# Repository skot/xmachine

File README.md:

# The SE/30 Xmachine
* 1989 Apple Macintosh SE/30
* MC68030 PDS Card
* Lattice ECP5 FPGA

## Files
* Eagle Schematic and PCB

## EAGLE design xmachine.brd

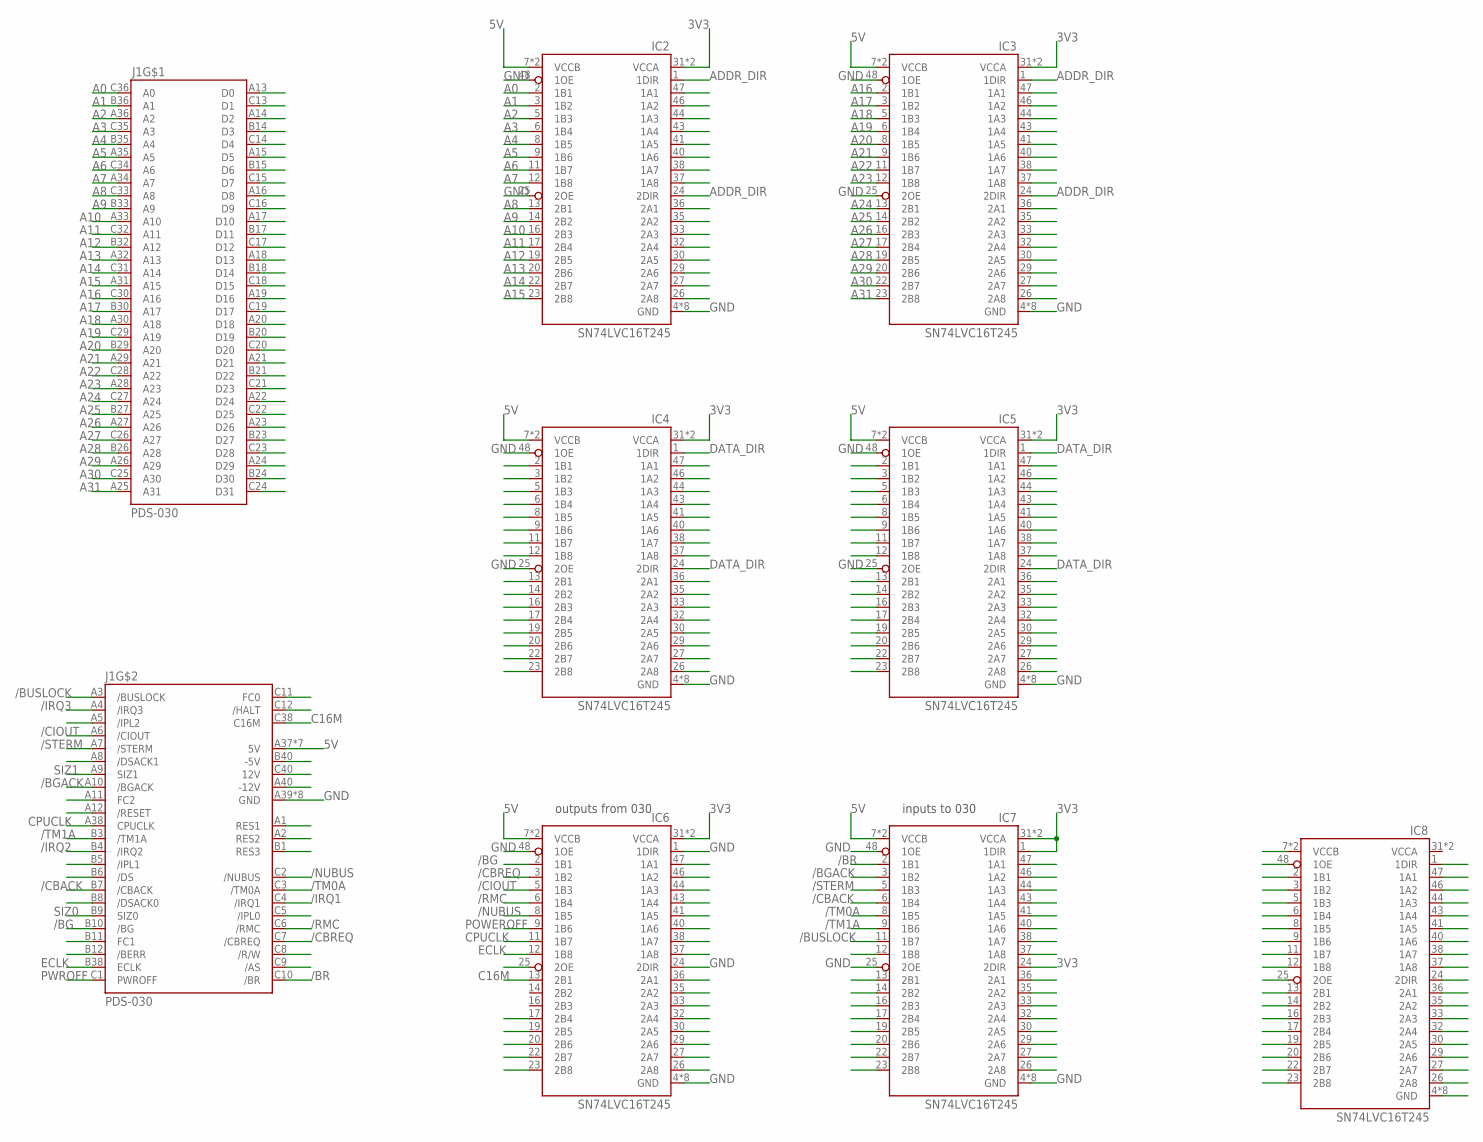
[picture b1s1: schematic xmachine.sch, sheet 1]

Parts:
IC2, IC3, IC4, IC5, IC6, IC7, IC8: SN74LVC16T245; SOP63P1035X279-48N
J1: PDS-030; 650906-5

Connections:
3V3: IC2.31 (VCCA), IC2.42 (VCCA), IC3.31 (VCCA), IC3.42 (VCCA), IC4.31 (VCCA), IC4.42 (VCCA), IC5.31 (VCCA), IC5.42 (VCCA), IC6.31 (VCCA), IC6.42 (VCCA), IC7.1 (1DIR), IC7.24 (2DIR), IC7.31 (VCCA), IC7.42 (VCCA); also elsewhere on the board
5V: IC2.7 (VCCB), IC2.18 (VCCB), IC3.7 (VCCB), IC3.18 (VCCB), IC4.7 (VCCB), IC4.18 (VCCB), IC5.7 (VCCB), IC5.18 (VCCB), IC6.7 (VCCB), IC6.18 (VCCB), IC7.7 (VCCB), IC7.18 (VCCB), J1.A37 (5V), J1.B13 (5V), J1.B19 (5V), J1.B25 (5V), J1.B31 (5V), J1.B37 (5V), J1.C37 (5V)
/BG: IC6.2 (1B1), J1.B10 (/BG)
/BGACK: IC7.3 (1B2), J1.A10 (/BGACK)
/BR: IC7.2 (1B1), J1.C10 (/BR)
/BUSLOCK: IC7.11 (1B7), J1.A3 (/BUSLOCK)
/CBACK: IC7.6 (1B4), J1.B7 (/CBACK)
/CBREQ: IC6.3 (1B2), J1.C7 (/CBREQ)
/CIOUT: IC6.5 (1B3), J1.A6 (/CIOUT)
/IRQ1: J1.C4 (/IRQ1)
/IRQ2: J1.B4 (/IRQ2)
/IRQ3: J1.A4 (/IRQ3)
/NUBUS: IC6.8 (1B5), J1.C2 (/NUBUS)
/RMC: IC6.6 (1B4), J1.C6 (/RMC)
/STERM: IC7.5 (1B3), J1.A7 (/STERM)
/TM0A: IC7.8 (1B5), J1.C3 (/TM0A)
/TM1A: IC7.9 (1B6), J1.B3 (/TM1A)
A0: IC2.2 (1B1), J1.C36 (A0)
A1: IC2.3 (1B2), J1.B36 (A1)
A2: IC2.5 (1B3), J1.A36 (A2)
A3: IC2.6 (1B4), J1.C35 (A3)
A4: IC2.8 (1B5), J1.B35 (A4)
A5: IC2.9 (1B6), J1.A35 (A5)
A6: IC2.11 (1B7), J1.C34 (A6)
A7: IC2.12 (1B8), J1.A34 (A7)
A8: IC2.13 (2B1), J1.C33 (A8)
A9: IC2.14 (2B2), J1.B33 (A9)
A10: IC2.16 (2B3), J1.A33 (A10)
A11: IC2.17 (2B4), J1.C32 (A11)
A12: IC2.19 (2B5), J1.B32 (A12)
A13: IC2.20 (2B6), J1.A32 (A13)
A14: IC2.22 (2B7), J1.C31 (A14)
A15: IC2.23 (2B8), J1.A31 (A15)
A16: IC3.2 (1B1), J1.C30 (A16)
A17: IC3.3 (1B2), J1.B30 (A17)
A18: IC3.5 (1B3), J1.A30 (A18)
A19: IC3.6 (1B4), J1.C29 (A19)
A20: IC3.8 (1B5), J1.B29 (A20)
A21: IC3.9 (1B6), J1.A29 (A21)
A22: IC3.11 (1B7), J1.C28 (A22)
A23: IC3.12 (1B8), J1.A28 (A23)
A24: IC3.13 (2B1), J1.C27 (A24)
A25: IC3.14 (2B2), J1.B27 (A25)
A26: IC3.16 (2B3), J1.A27 (A26)
A27: IC3.17 (2B4), J1.C26 (A27)
A28: IC3.19 (2B5), J1.B26 (A28)
A29: IC3.20 (2B6), J1.A26 (A29)
A30: IC3.22 (2B7), J1.C25 (A30)
A31: IC3.23 (2B8), J1.A25 (A31)
ADDR_DIR: IC2.1 (1DIR), IC2.24 (2DIR), IC3.1 (1DIR), IC3.24 (2DIR)
C16M: IC6.13 (2B1), J1.C38 (C16M)
CPUCLK: IC6.11 (1B7), J1.A38 (CPUCLK)
DATA_DIR: IC4.1 (1DIR), IC4.24 (2DIR), IC5.1 (1DIR), IC5.24 (2DIR)
ECLK: IC6.12 (1B8), J1.B38 (ECLK)
GND: IC2.4 (GND), IC2.10 (GND), IC2.15 (GND), IC2.21 (GND), IC2.25 (2OE), IC2.28 (GND), IC2.34 (GND), IC2.39 (GND), IC2.45 (GND), IC2.48 (1OE), IC3.4 (GND), IC3.10 (GND), IC3.15 (GND), IC3.21 (GND), IC3.25 (2OE), IC3.28 (GND), IC3.34 (GND), IC3.39 (GND), IC3.45 (GND), IC3.48 (1OE), IC4.4 (GND), IC4.10 (GND), IC4.15 (GND), IC4.21 (GND), IC4.25 (2OE), IC4.28 (GND), IC4.34 (GND), IC4.39 (GND), IC4.45 (GND), IC4.48 (1OE), IC5.4 (GND), IC5.10 (GND), IC5.15 (GND), IC5.21 (GND), IC5.25 (2OE), IC5.28 (GND), IC5.34 (GND), IC5.39 (GND), IC5.45 (GND), IC5.48 (1OE), IC6.1 (1DIR), IC6.4 (GND), IC6.10 (GND), IC6.15 (GND), IC6.21 (GND), IC6.24 (2DIR), IC6.28 (GND), IC6.34 (GND), IC6.39 (GND), IC6.45 (GND), IC6.48 (1OE), IC7.4 (GND), IC7.10 (GND), IC7.15 (GND), IC7.21 (GND), IC7.25 (2OE), IC7.28 (GND), IC7.34 (GND), IC7.39 (GND), IC7.45 (GND), IC7.48 (1OE), J1.A39 (GND), J1.B2 (GND), J1.B16 (GND), J1.B22 (GND), J1.B28 (GND), J1.B34 (GND), J1.B39 (GND), J1.C39 (GND); also elsewhere on the board
unnamed: IC8.4 (GND), IC8.10 (GND), IC8.15 (GND), IC8.21 (GND), IC8.28 (GND), IC8.34 (GND), IC8.39 (GND), IC8.45 (GND)
unnamed: IC8.7 (VCCB), IC8.18 (VCCB)
POWEROFF: IC6.9 (1B6)
PWROFF: J1.C1 (PWROFF)
SIZ0: J1.B9 (SIZ0)
SIZ1: J1.A9 (SIZ1)

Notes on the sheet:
outputs from 030
inputs to 030

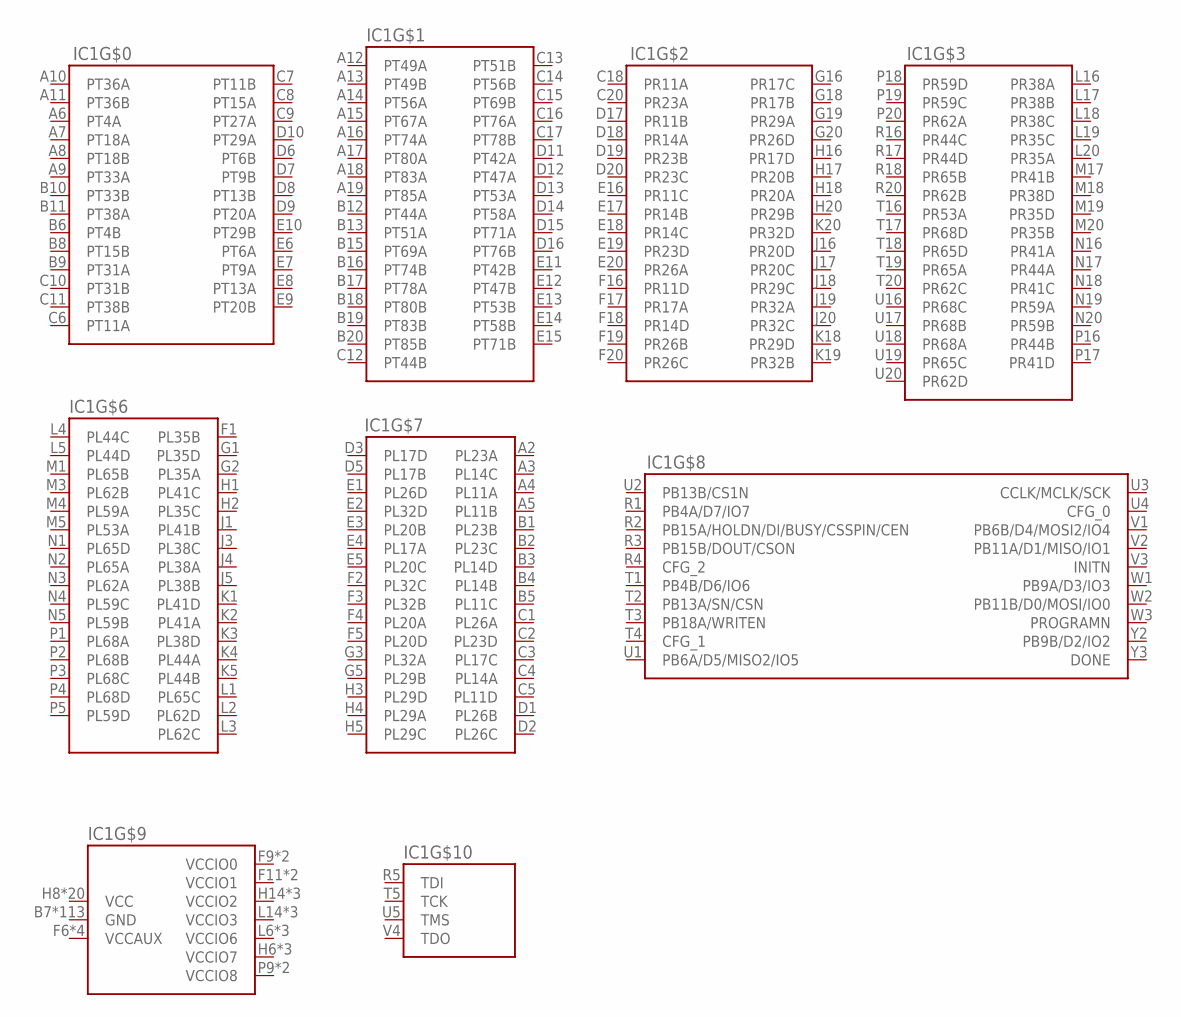
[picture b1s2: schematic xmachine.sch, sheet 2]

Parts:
IC1: ECP5-LFE5U-XXF-8BG381C; BGA400C80P20X20_1700X1700X176N

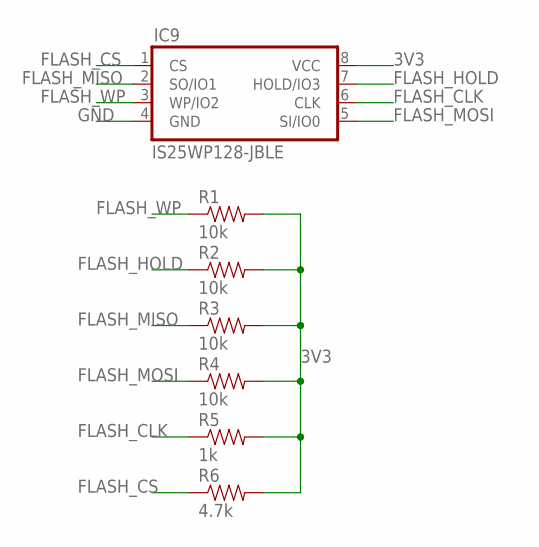
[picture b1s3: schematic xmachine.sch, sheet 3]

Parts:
IC9: IS25WP128-JBLE; SOIC127P790X216-8N; PARTNO IS25WP128-JBLE
R1, R2, R3, R4: 10k; R0402
R5: 1k; R0402
R6: 4.7k; R0402

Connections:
3V3: IC9.8 (VCC), R1.2, R2.2, R3.2, R4.2, R5.2, R6.2; also elsewhere on the board
FLASH_CLK: IC9.6 (CLK), R5.1
FLASH_CS: IC9.1 (CS), R6.1
FLASH_HOLD: IC9.7 (HOLD/IO3), R2.1
FLASH_MISO: IC9.2 (SO/IO1), R3.1
FLASH_MOSI: IC9.5 (SI/IO0), R4.1
FLASH_WP: IC9.3 (WP/IO2), R1.1
GND: IC9.4 (GND); also elsewhere on the board

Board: 4 copper layers, 16 parts (0 on the bottom side), 60 nets, no tracks yet.

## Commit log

2020-04-04 initial import
2020-04-04 added some docs
2020-04-10 added level shifters and flash memory
